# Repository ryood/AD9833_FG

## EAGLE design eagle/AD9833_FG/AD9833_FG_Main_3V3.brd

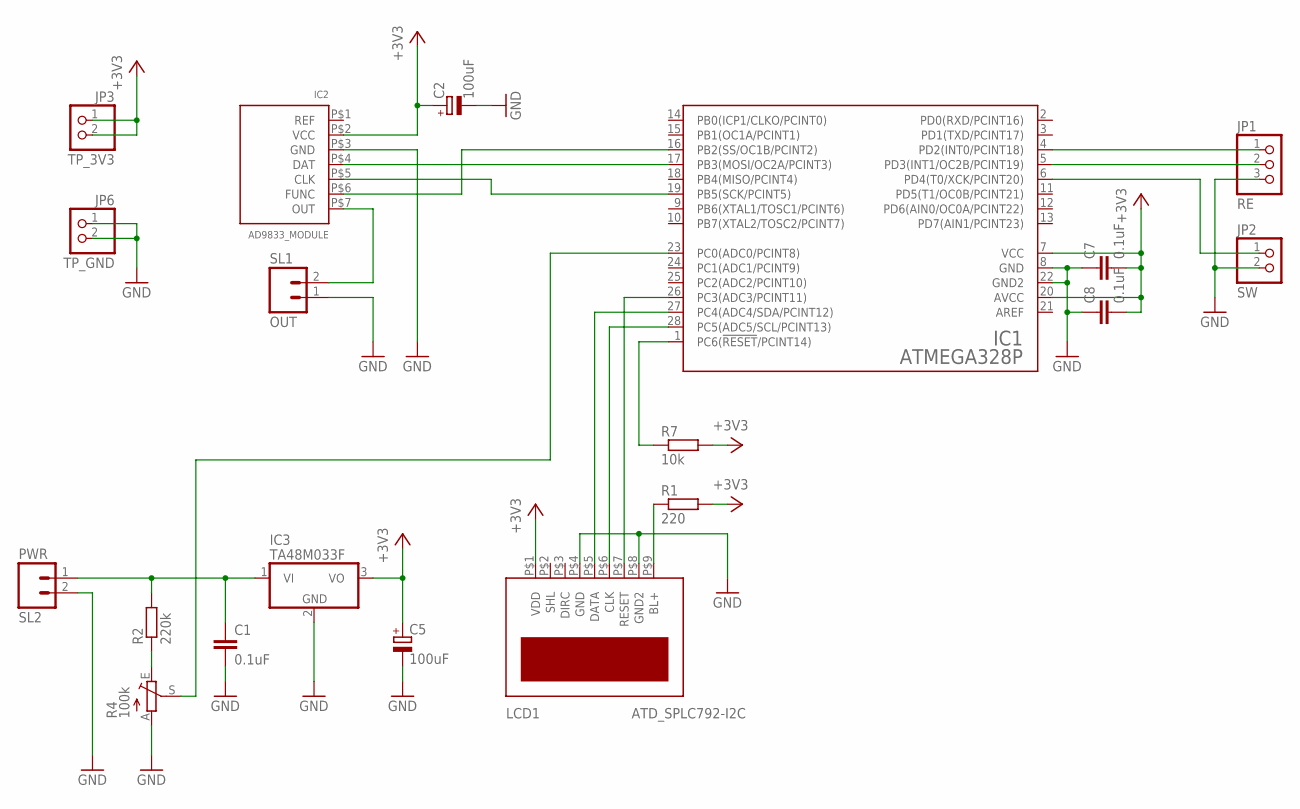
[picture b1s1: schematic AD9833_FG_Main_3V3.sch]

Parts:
C1, C7: 0.1uF; C025-024X044
C2: 100uF; SANYO-OSCON_C
C5: 100uF; E2,5-7
C8: 0.1uF; C050-024X044
IC1: ATMEGA328P; DIL28-3
IC2: AD9833_MODULE
IC3: TA48M033F; TA48MXXX
JP1: RE; 1X03
JP2: SW; 1X02
JP3: TP_3V3; 1X02
JP6: TP_GND; 1X02
LCD1: ATD_SPLC792-I2C
R1: 220; 0207/7
R2: 220k; 0207/7
R4: 100k; B25P
R7: 10k; 0207/7
SL1: OUT; 02P
SL2: PWR; 02P

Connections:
+3V3: C2.+, C5.+, C7.2, C8.2, IC1.7 (VCC), IC1.20 (AVCC), IC2.P$2 (VCC), IC3.3 (VO), JP3.1, JP3.2, LCD1.P$1 (VDD), R1.2, R7.2
GND: C1.2, C2.-, C5.-, C7.1, C8.1, IC1.8 (GND), IC1.22 (GND2), IC2.P$3 (GND), IC3.2 (GND), JP1.3, JP2.2, JP6.1, JP6.2, LCD1.P$4 (GND), LCD1.P$8 (GND2), R4.A, SL1.1, SL2.2
unnamed: IC1.17 (PB3(MOSI/OC2A/PCINT3)), IC2.P$4 (DAT)
unnamed: IC1.19 (PB5(SCK/PCINT5)), IC2.P$5 (CLK)
unnamed: IC1.16 (PB2(SS/OC1B/PCINT2)), IC2.P$6 (FUNC)
unnamed: IC1.28 (PC5(ADC5/SCL/PCINT13)), LCD1.P$6 (CLK)
unnamed: IC1.27 (PC4(ADC4/SDA/PCINT12)), LCD1.P$5 (DATA)
unnamed: IC2.P$7 (OUT), SL1.2
unnamed: IC1.26 (PC3(ADC3/PCINT11)), LCD1.P$7 (RESET)
unnamed: IC1.4 (PD2(INT0/PCINT18)), JP1.1
unnamed: IC1.5 (PD3(INT1/OC2B/PCINT19)), JP1.2
unnamed: IC1.6 (PD4(T0/XCK/PCINT20)), JP2.1
unnamed: R2.1, R4.E
unnamed: LCD1.P$9 (BL+), R1.1
unnamed: C1.1, IC3.1 (VI), R2.2, SL2.1
unnamed: IC1.23 (PC0(ADC0/PCINT8)), R4.S
unnamed: IC1.1 (PC6(!RESET!/PCINT14)), R7.1

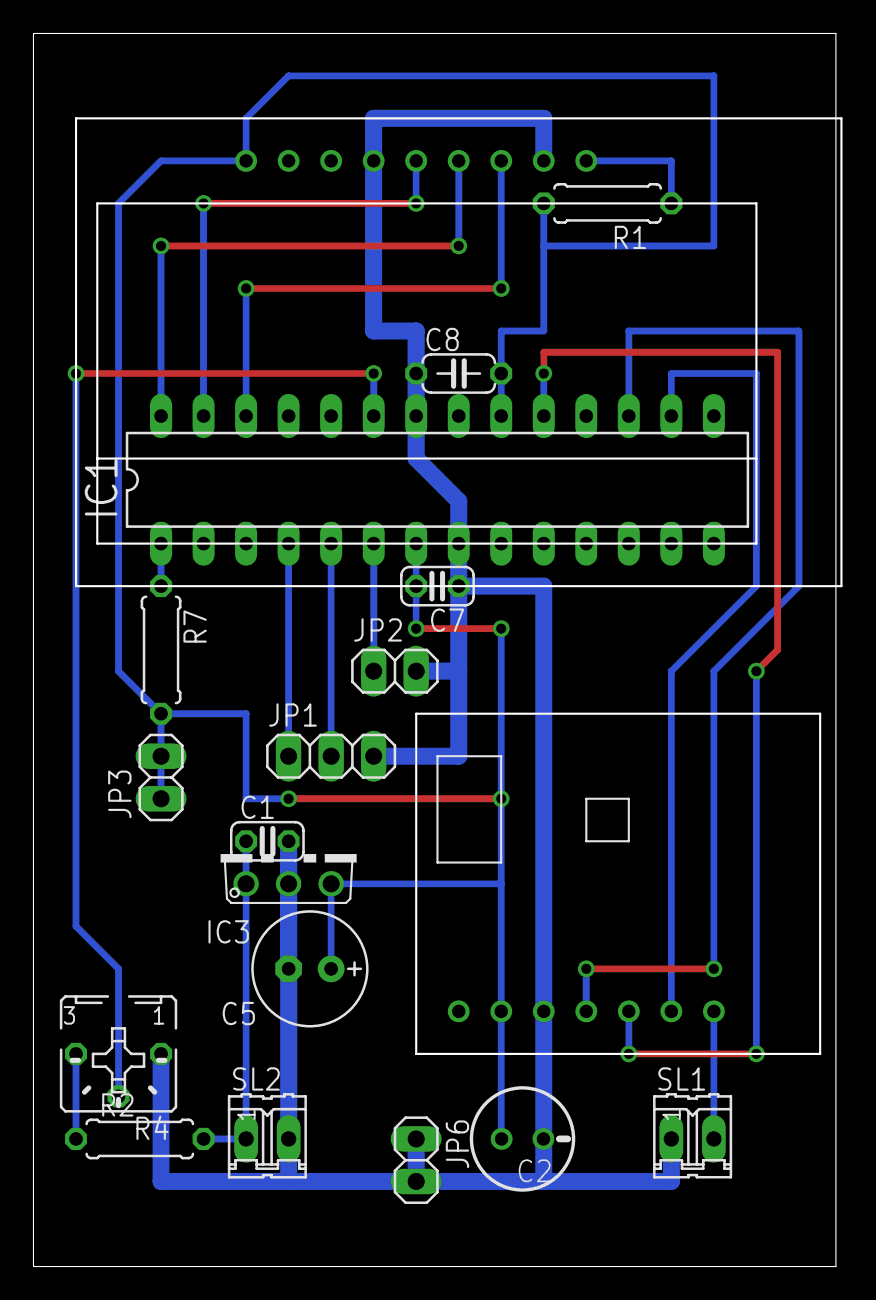
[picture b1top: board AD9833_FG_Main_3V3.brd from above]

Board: 2 copper layers, 48.2 x 73.5 mm, 19 parts (0 on the bottom side), 17 nets.

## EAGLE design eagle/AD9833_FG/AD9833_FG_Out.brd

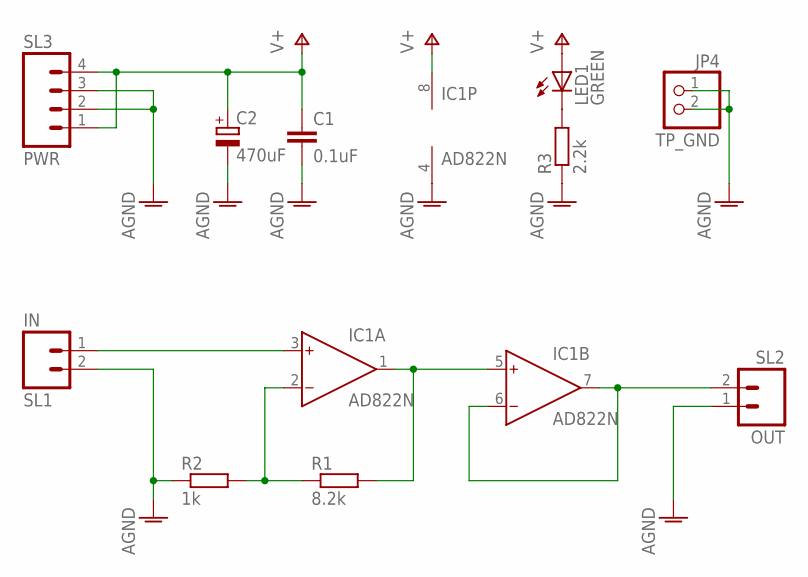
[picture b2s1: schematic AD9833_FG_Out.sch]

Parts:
C1: 0.1uF; C025-024X044
C2: 470uF; E2,5-7
IC1: AD822N; DIL08
JP4: TP_GND; 1X02
LED1: GREEN; LED3MM
R1: 8.2k; 0207/7
R2: 1k; 0207/7
R3: 2.2k; 0207/7
SL1: IN; 02P
SL2: OUT; 02P
SL3: PWR; 04P

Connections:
AGND: C1.2, C2.-, IC1.4 (V-), JP4.1, JP4.2, R2.1, R3.1, SL1.2, SL2.1, SL3.2, SL3.3
unnamed: IC1.2 (IN-), R1.1, R2.2
unnamed: IC1.3 (IN+), SL1.1
unnamed: IC1.1 (OUT), IC1.5 (IN+), R1.2
unnamed: IC1.6 (IN-), IC1.7 (OUT), SL2.2
unnamed: LED1.K (C), R3.2
V+: C1.1, C2.+, IC1.8 (V+), LED1.A, SL3.1, SL3.4

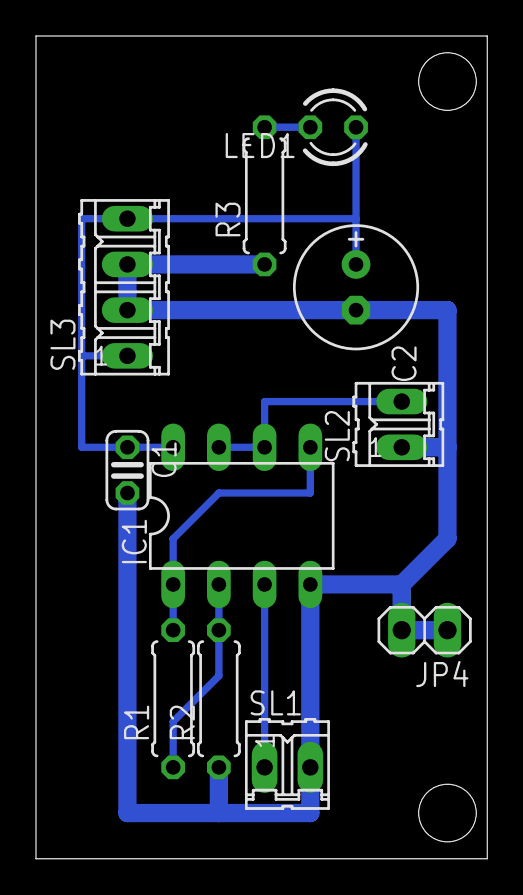
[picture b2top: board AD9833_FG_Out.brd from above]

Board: 2 copper layers, 25.1 x 45.7 mm, 11 parts (0 on the bottom side), 7 nets.

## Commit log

2017-07-24 Impl: I2C LCD
2017-07-24 Debug: UI_Test: I2C-LCD
2017-07-24 Add: AD9833_FG.ino
2017-07-24 AD9833_FG: Clean up
2017-07-24 AD9833_FG: Wave Out & LCD Display
2017-07-24 AD9833_FG: 周波数刻みを増やした
2017-07-26 Update AD9833_FG.ino Add eagle & spice files
2017-07-26 AD9833_FG impl. EEPROM
2017-07-27 AD9833_FG Impl. Battery Check
2017-07-27 AD9833_FG 波形選択用SWをタクトスイッチからトグルスイッチに変更
2017-07-28 Add eagle files
2017-07-29 Update eagle files
2017-07-29 Add ケース内配線
2017-07-29 3.3V Version
2017-07-29 8MHz Version (No XTAL)
2017-07-29 Board Design
2017-07-30 Battery check -> percentage
2017-08-06 Impl. Amp Board
2017-08-07 Update firamware
2018-10-31 Add: a Image
2018-10-31 10, 12, 15, 25, 30 ...
